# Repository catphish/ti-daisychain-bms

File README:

TI Daisychain BMS Master
========================

BMS master for daisychained bq76PL455A slave modules.

Building the Firmware
=====================

Prerequisites
-------------

The following tools must be installed before building:

- CMake (https://cmake.org/download/)
- Ninja build system (https://github.com/ninja-build/ninja/releases)
- GNU Arm Embedded Toolchain / arm-none-eabi-gcc
  (https://developer.arm.com/tools-and-software/open-source-software/developer-tools/gnu-toolchain/gnu-rm)
- Raspberry Pi Pico SDK (https://github.com/raspberrypi/pico-sdk)
- Raspberry Pi Pico Extras (https://github.com/raspberrypi/pico-extras)

After installing the Pico SDK and Pico Extras, set the following environment
variables so CMake can find them:

  Windows (Command Prompt):
    set PICO_SDK_PATH=C:\path\to\pico-sdk
    set PICO_EXTRAS_PATH=C:\path\to\pico-extras

  Linux / macOS:
    export PICO_SDK_PATH=/path/to/pico-sdk
    export PICO_EXTRAS_PATH=/path/to/pico-extras

Building with VS Code
---------------------

1. Open the firmware-pico folder in VS Code
   (File > Open Folder... > select firmware-pico)
2. Install the recommended extensions when prompted
   (ms-vscode.cmake-tools, ms-vscode.cpptools, marus25.cortex-debug,
    raspberry-pi.raspberry-pi-pico)
3. When prompted, select the ARM GCC toolchain kit
4. Run Terminal > Run Build Task (Ctrl+Shift+B) to configure and build

The compiled firmware files (bms.uf2, bms.elf, etc.) will be placed in the
firmware-pico/build directory.

Building from the Command Line
-------------------------------

The following commands use the same build flags as settings.json. If you
change cmake.buildDirectory or cmake.configureArgs in settings.json, update
these commands accordingly:

  cd firmware-pico
  cmake -B build -G Ninja -DPICO_BOARD=pico -DCMAKE_BUILD_TYPE=Release
  cmake --build build

Uploading to the Pico
---------------------

Hold the BOOTSEL button on the Pico and connect it to your PC via USB. It
will appear as a mass-storage device (RPI-RP2). Copy firmware-pico/build/bms.uf2
to that drive. The Pico will reboot and run the new firmware automatically.

This board will communicate with up to 3 strings of bq76PL455A battery
modules. Each string supports up to 16 modules, and each module supports
up to 16 cells. A common configuration is 3 strings of 6 modules but any
combination is supported.

The board will read the voltages of all detected cells and will perform
balancing as well as reporting data over CAN.

Connector J1
=============

------------------------
| CANH | WAKE1 | WAKE2 |
| CANL |  GND  |  +12V |
------------------------

The low voltage connector J1 has 3 functions:

1) Connect +12v to a permanent positive suppy (5v - 14v)
2) Connect CANH and CANL to a CAN bus.
3) Connect WAKE1 and WAKE2 to switched voltage sources

If either WAKE1 OR WAKE2 is live (+5v to +14v) theh the board will wake
up and monitor the pack. If both are off (0v) then the board will finish
any in-progress balancing, then go into a low power sleep mode.

It is recommended to connect WAKE1 to ignition live, and WAKE2 to a 12V
output generated by a charger. This will ensure that the cells are monitored
during both charge and discharge.

Connector J2, J3, J4
====================

Each of the BATT1, BATT2 and BATT3 (J2,J3,J4) may be connected to the data
pins of a bq76PL455A battery module. All three are optional, and all three
support a full chain of up to 16 battery modules, or any partial chain.
Chain lengths do not have to be matched. The pinout of the battery module
is beyong the scope of this document.

Power Modes
===========

When either WAKE1 or WAKE2 are high, the module will enter active mode. In
this mode, it will continuously monitor the voltage of all attached cells.
Data including the pack voltage, high and low cell voltages, and temperatures
will be send to the CAN bus at 1 second intervals. Balancing will take place
if necessary. For further details of balancing see the next section.

When WAKE1 and WAKE2 are both low, and balancing is complete, the board will
enter a low power sleep mode. In this mode, the board consumes approximately
600uA (0.6mA) at 12V and will perform no actions until woken again. The
bq76PL455A modules will also anter a low power state, consuming close to zero
power from the high voltage pack.

Balancing
=========

If any cell voltage is detected as being higher than 4.0V and more than 10mV
higher than the lowest recorded cell voltage, it will be bled until one of
these ocnditions is no longer met. To prevent excessive heat, only one cell
in each battery (16 cell module) will be bled simultaneously. If multiple cells
meet the criteria, the cell with the highest voltage will be selected.
Balancing will be considered complete when no cells meet the criteria for
balancing.

CAN Messages Received
=====================

This modules does not receive CAN messages.

CAN Messages Sent
=================

--------------------------------------------------------------------------------
| CAN ID | Byte 0-3           | Byte 4-5          | Byte 6      | Byte 7       |
| 0x4f0  | Total Pack Voltage | Balance Threshold | Error count | Module count |
--------------------------------------------------------------------------------

Total pack voltage it the sum of all modules. For parallel packs this value
will be a multiple of the real pack voltage.

Balance threshold will be a non-zero value when balancing is active and
indicates the target voltage, generally this will be 10mV higher than the
minimum cell voltage.

--------------------------------------------------------------------
| CAN ID | Byte 0-1   | Byte 2-3   | Byte 4-5      | Byte 6-7      |
| 0x4f1  | Max Cell V | Min Cell V | Max Cell Temp | Min Cell Temp |
--------------------------------------------------------------------

All values are big endian. Voltage values should be interpreted by dividing
the value by 13107. Temperature values are 

The following calculation can be used to convert the readong for an External NTC to a temperature:

float temperature(uint16_t adc) {
  float r = 0.0000000347363427499292f * adc * adc - 0.001025770762903f * adc + 2.68235340614337f;
  float t = log(r) * -30.5280964239816f + 95.6841501312447f;
  return t;
}

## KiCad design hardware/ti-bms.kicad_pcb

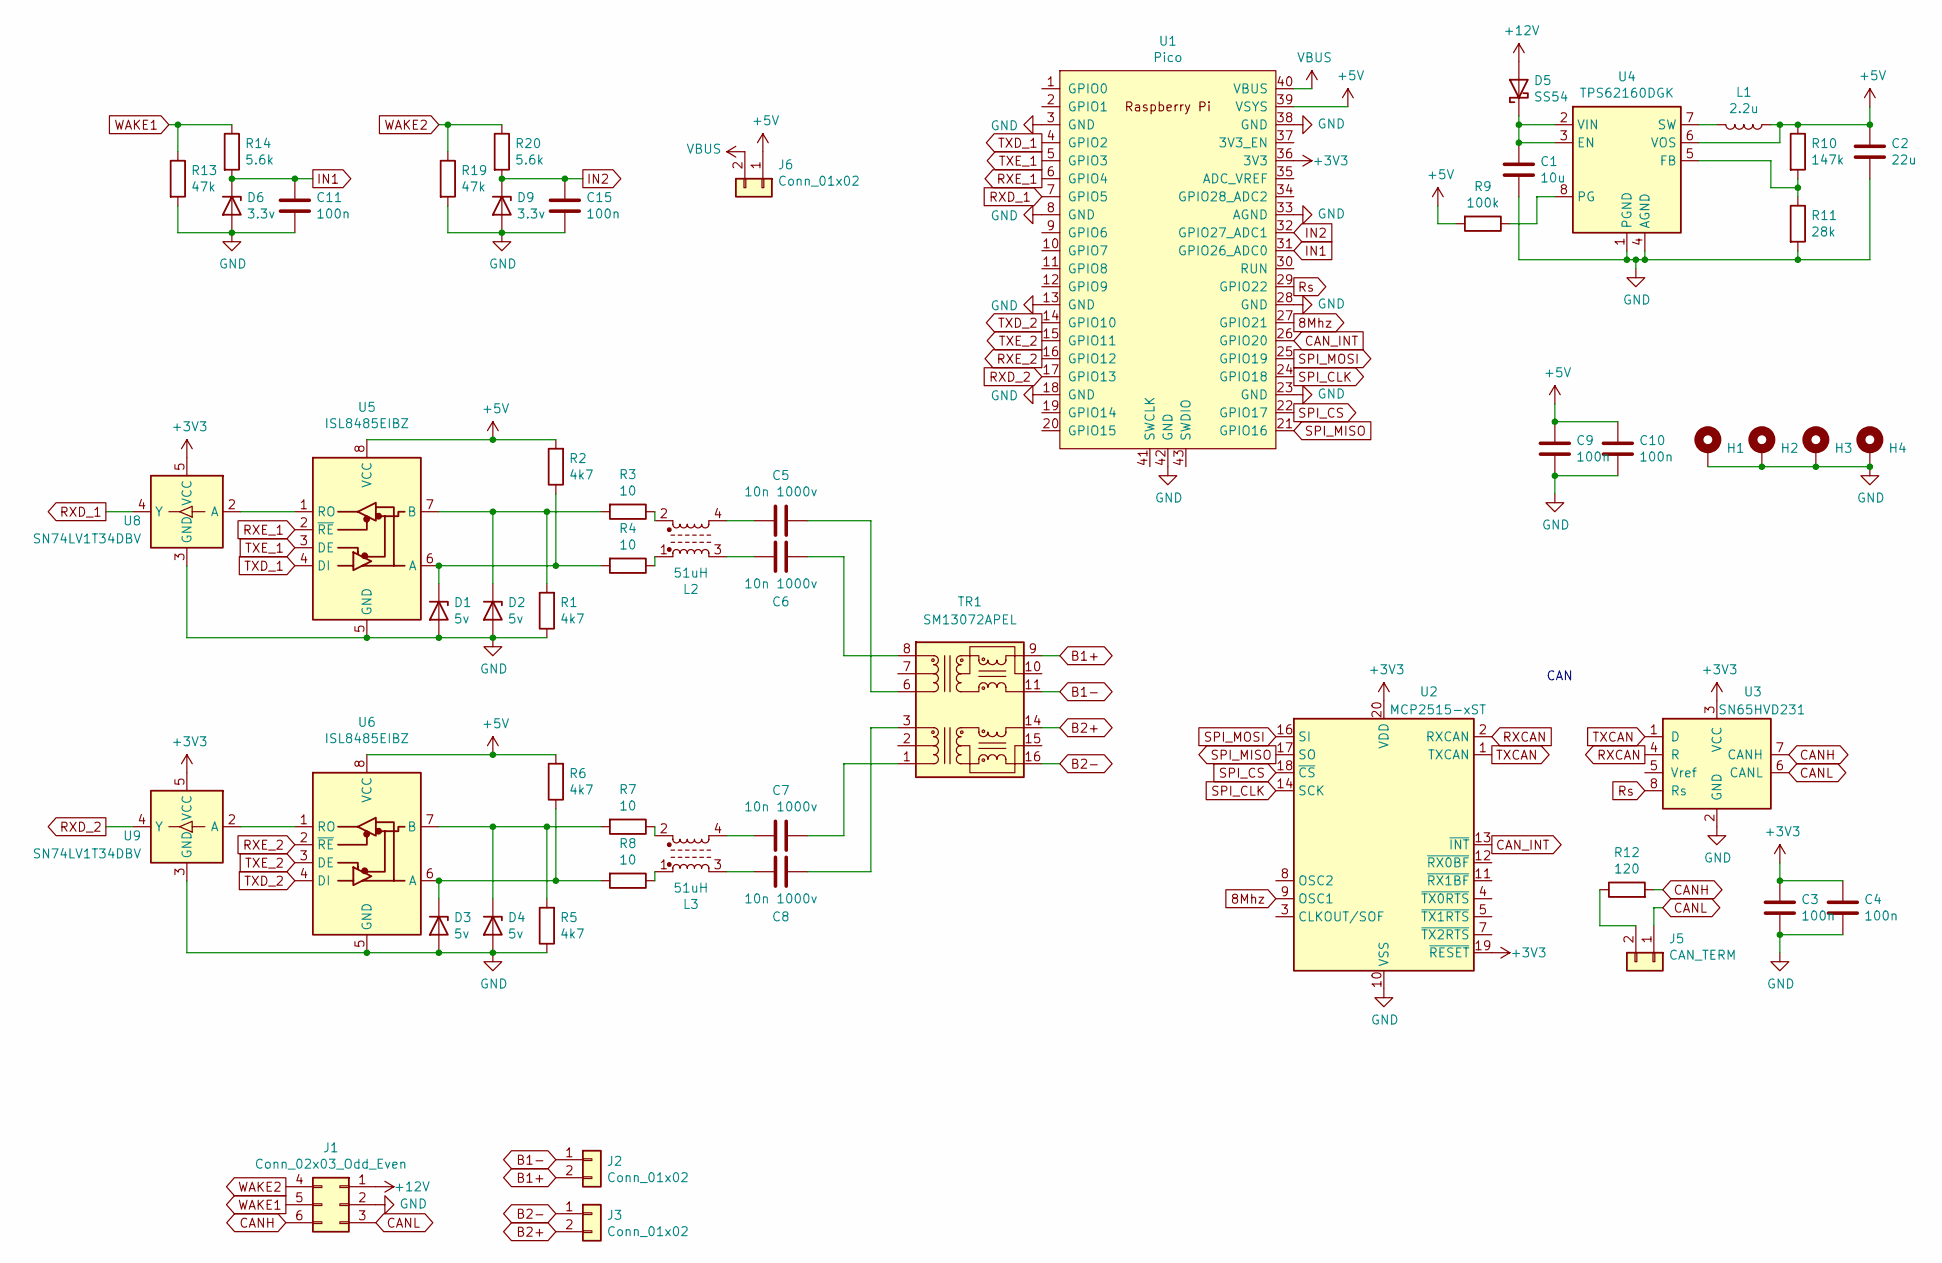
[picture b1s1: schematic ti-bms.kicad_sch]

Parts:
C1: 10u; C_1210_3225Metric; LCSC C77102
C2: 22u; C_1206_3216Metric; LCSC C5672
C3, C4, C9, C10, C11, C15: 100n; C_0603_1608Metric; LCSC C14663
C5, C6, C7, C8: 10n 1000v; C_1206_3216Metric; LCSC C9194
D1, D2, D3, D4: 5v; SOD882; LCSC C85401
D5: SS54; D_SMA; LCSC C22452
D6, D9: 3.3v; D_MiniMELF; LCSC C8056
H1, H2, H3, H4: MountingHole; MountingHole_3.2mm_M3_Pad
J1: Conn_02x03_Odd_Even; Molex_Micro-Fit_3.0_43045-0600_2x03_P3.00mm_Horizontal
J2, J3: Conn_01x02; Molex_Micro-Fit_3.0_43650-0200_1x02_P3.00mm_Horizontal
J5: CAN_TERM; PinHeader_1x02_P2.54mm_Vertical
J6: Conn_01x02; PinHeader_1x02_P2.54mm_Vertical
L1: 2.2u; L_Neosid_SMS-ME3015; LCSC C43389
L2, L3: 51uH; ACT45B-101-2P-TL003; LCSC C76584
R1, R2, R5, R6: 4k7; R_0603_1608Metric; LCSC C23162
R3, R4, R7, R8: 10; R_0603_1608Metric; LCSC C22859
R9: 100k; R_0603_1608Metric; LCSC C25803
R10: 147k; R_0603_1608Metric; LCSC C22878
R11: 28k; R_0603_1608Metric; LCSC C22989
R12: 120; R_1206_3216Metric; LCSC C17909
R13, R19: 47k; R_0603_1608Metric; LCSC C25819
R14, R20: 5.6k; R_0603_1608Metric; LCSC C23189
TR1: SM13072APEL; Transformer_Ethernet_Wuerth_749013011A; LCSC C129155
U1: Pico; RPi_Pico_SMD_TH
U2: MCP2515-xST; TSSOP-20_4.4x6.5mm_P0.65mm; LCSC C15193
U3: SN65HVD231; SOIC-8_3.9x4.9mm_P1.27mm; LCSC C129257
U4: TPS62160DGK; MSOP-8_3x3mm_P0.65mm; LCSC C60726
U5, U6: ISL8485EIBZ; SOP-8_3.9x4.9mm_P1.27mm; LCSC C382024
U8, U9: SN74LV1T34DBV; SOT-23-5; LCSC C100024

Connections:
8Mhz: U1.27 (GPIO21), U2.9 (OSC1)
+3V3: C3.1, C4.1, U1.36 (3V3), U2.19 (~RESET), U2.20 (VDD), U3.3 (VCC), U8.5 (VCC), U9.5 (VCC)
+5V: C2.1, C9.1, C10.1, J6.1, L1.1, R2.2, R6.2, R9.2, R10.1, U1.39 (VSYS), U4.6 (VOS), U5.8 (VCC), U6.8 (VCC)
+12V: D5.2 (A), J1.1
B1+: J2.2, TR1.9 (RX-)
B1-: J2.1, TR1.11 (RX+)
B2+: J3.2, TR1.14 (TX-)
B2-: J3.1, TR1.16 (TX+)
CANH: J1.6, R12.2, U3.7 (CANH)
CANL: J1.3, J5.1, U3.6 (CANL)
CAN_INT: U1.26 (GPIO20), U2.13 (~INT)
GND: C1.2, C2.2, C3.2, C4.2, C9.2, C10.2, C11.2, C15.2, D1.2 (A), D2.2 (A), D3.2 (A), D4.2 (A), D6.2 (A), D9.2 (A), H1.1, H2.1, H3.1, H4.1, J1.2, R1.1, R5.1, R11.2, R13.2, R19.2, U1.3 (GND), U1.8 (GND), U1.13 (GND), U1.18 (GND), U1.23 (GND), U1.28 (GND), U1.33 (AGND), U1.38 (GND), U1.42 (GND), U2.10 (VSS), U3.2 (GND), U4.1 (PGND), U4.4 (AGND), U5.5 (GND), U6.5 (GND), U8.3 (GND), U9.3 (GND)
IN1: C11.1, D6.1 (K), R14.2, U1.31 (GPIO26_ADC0)
IN2: C15.1, D9.1 (K), R20.2, U1.32 (GPIO27_ADC1)
unnamed: C1.1, D5.1 (K), U4.2 (VIN), U4.3 (EN)
unnamed: C5.1, TR1.6 (RD+)
unnamed: C5.2, L2.4
unnamed: C6.1, TR1.8 (RD-)
unnamed: C6.2, L2.3
unnamed: C7.1, TR1.1 (TD+)
unnamed: C7.2, L3.4
unnamed: C8.1, TR1.3 (TD-)
unnamed: C8.2, L3.3
unnamed: D1.1 (K), R2.1, R4.2, U5.6 (A)
unnamed: D2.1 (K), R1.2, R3.2, U5.7 (B)
unnamed: D3.1 (K), R6.1, R8.2, U6.6 (A)
unnamed: D4.1 (K), R5.2, R7.2, U6.7 (B)
unnamed: J5.2, R12.1
unnamed: L1.2, U4.7 (SW)
unnamed: L2.1, R4.1
unnamed: L2.2, R3.1
unnamed: L3.1, R8.1
unnamed: L3.2, R7.1
unnamed: R9.1, U4.8 (PG)
unnamed: R10.2, R11.1, U4.5 (FB)
unnamed: U5.1 (RO), U8.2 (A)
unnamed: U6.1 (RO), U9.2 (A)
RXCAN: U2.2 (RXCAN), U3.4 (R)
RXD_1: U1.7 (GPIO5), U8.4 (Y)
RXD_2: U1.17 (GPIO13), U9.4 (Y)
RXE_1: U1.6 (GPIO4), U5.2 (~RE)
RXE_2: U1.16 (GPIO12), U6.2 (~RE)
Rs: U1.29 (GPIO22), U3.8 (Rs)
SPI_CLK: U1.24 (GPIO18), U2.14 (SCK)
SPI_CS: U1.22 (GPIO17), U2.18 (~CS)
SPI_MISO: U1.21 (GPIO16), U2.17 (SO)
SPI_MOSI: U1.25 (GPIO19), U2.16 (SI)
TXCAN: U2.1 (TXCAN), U3.1 (D)
TXD_1: U1.4 (GPIO2), U5.4 (DI)
TXD_2: U1.14 (GPIO10), U6.4 (DI)
TXE_1: U1.5 (GPIO3), U5.3 (DE)
TXE_2: U1.15 (GPIO11), U6.3 (DE)
VBUS: J6.2, U1.40 (VBUS)
WAKE1: J1.5, R13.1, R14.1
WAKE2: J1.4, R19.1, R20.1

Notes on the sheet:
CAN

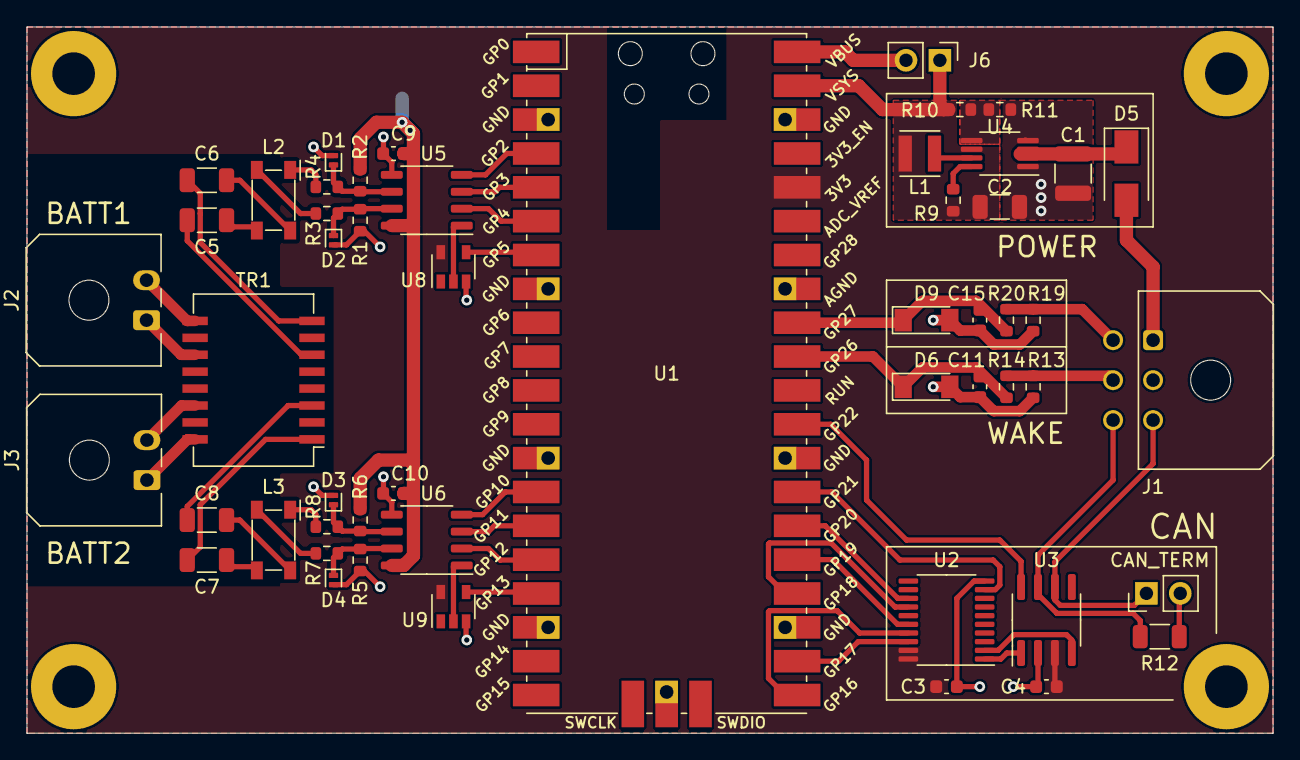
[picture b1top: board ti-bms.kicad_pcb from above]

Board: 2 copper layers, 93.5 x 53.0 mm, 56 parts (0 on the bottom side), 55 nets.

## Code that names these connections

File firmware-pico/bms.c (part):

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#define MAX_MODULES (16 * CHAIN_COUNT)

// Hardware wakeup pins
#define WAKE1 26
#define WAKE2 27

// Define pins for SPI (to CAN)
#define SPI_PORT spi0
#define SPI_MISO 16
#define SPI_CS 17
#define SPI_CLK 18
#define SPI_MOSI 19
#define CAN_INT 20    // Interrupt from CAN controller
#define CAN_CLK 21    // 8MHz clock for CAN
#define CAN_SLEEP 22  // Shut down CAN transceiver

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void SPI_configure() {
  spi_init(SPI_PORT, 1000000);
  spi_set_format(SPI_PORT, 8, 0, 0, SPI_MSB_FIRST);
  gpio_set_function(SPI_MISO, GPIO_FUNC_SPI);
  gpio_set_function(SPI_MOSI, GPIO_FUNC_SPI);
  gpio_set_function(SPI_CLK, GPIO_FUNC_SPI);
  gpio_init(SPI_CS);
  gpio_set_dir(SPI_CS, GPIO_OUT);
  gpio_put(SPI_CS, 1);
}

void CAN_reset() {
  gpio_put(SPI_CS, 0);
  spi_write_blocking(SPI_PORT, (uint8_t[]){CMD_RESET}, 1);
  gpio_put(SPI_CS, 1);
  busy_wait_us(100);
}

uint8_t CAN_reg_read(uint8_t reg) {
  uint8_t data;
  gpio_put(SPI_CS, 0);
  spi_write_blocking(SPI_PORT, (uint8_t[]){CMD_READ, reg}, 2);
  spi_read_blocking(SPI_PORT, 0, &data, 1);
  gpio_put(SPI_CS, 1);
  return (data);
}

void CAN_reg_write(uint8_t reg, uint8_t val) {
  gpio_put(SPI_CS, 0);
  spi_write_blocking(SPI_PORT, (uint8_t[]){CMD_WRITE, reg, val}, 3);
  gpio_put(SPI_CS, 1);
}

void CAN_reg_modify(uint8_t reg, uint8_t mask, uint8_t val) {
  gpio_put(SPI_CS, 0);
  busy_wait_us(2);
  spi_write_blocking(SPI_PORT, (uint8_t[]){CMD_MODIFY, reg, mask, val}, 4);
  busy_wait_us(2);
  gpio_put(SPI_CS, 1);
}

void CAN_configure(uint16_t id) {
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  CAN_reg_write(REG_CANCTRL, MODE_SLEEP);
  gpio_put(CAN_SLEEP, 1);  // Sleep the CAN transceiver
  uint32_t s = save_and_disable_interrupts();
  gpio_set_irq_enabled_with_callback(WAKE1, GPIO_IRQ_LEVEL_HIGH, true, &gpio_callback);
  gpio_set_irq_enabled_with_callback(WAKE2, GPIO_IRQ_LEVEL_HIGH, true, &gpio_callback);
  gpio_set_dormant_irq_enabled(WAKE1, GPIO_IRQ_LEVEL_HIGH, true);
  gpio_set_dormant_irq_enabled(WAKE2, GPIO_IRQ_LEVEL_HIGH, true);
  clocks_hw->sleep_en0 = 0;
  clocks_hw->sleep_en1 = 0;
  xosc_dormant();
  reconfigure_clocks();
  gpio_set_irq_enabled_with_callback(WAKE1, GPIO_IRQ_LEVEL_HIGH, false, &gpio_callback);
  gpio_set_irq_enabled_with_callback(WAKE2, GPIO_IRQ_LEVEL_HIGH, false, &gpio_callback);
  restore_interrupts(s);
  SPI_configure();
  gpio_put(CAN_SLEEP, 0);  // Wake the CAN transceiver
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  }

  // Configure hardware wakeup pins
  gpio_init(WAKE1);
  gpio_init(WAKE2);
  gpio_set_dir(WAKE1, GPIO_IN);
  gpio_set_dir(WAKE2, GPIO_IN);
  gpio_disable_pulls(WAKE1);
  gpio_disable_pulls(WAKE2);

  // Configure CAN transceiver sleep line
  gpio_init(CAN_SLEEP);
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    // Sleep for a minimum of 500ms second per loop.
    sleep_ms(500);
    // If there's no reason to be awake, go into very low power sleep
    if (!balance_threshold && !gpio_get(WAKE1) && !gpio_get(WAKE2) && usb_suspended()) {
      sleep_modules();
      deep_sleep();
      rewake = 1;
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
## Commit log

2021-12-23 initial comit
2021-12-24 remove fill from isolated area
2021-12-24 add missing 3d models
2021-12-24 more on isolation
2022-01-02 add firmware
2022-01-04 add readme, add CAN based wakeup
2022-01-04 correct voltage conversion value
2022-01-08 add 12v input and output, connect CAN line driver sleep pin
2022-01-10 dual wake inputs
2022-01-10 update schematic and picture
2022-01-12 rework inputs
2022-01-13 finish inputs
2022-01-25 swap in available part
2022-01-25 finish v3 firmware
2022-01-25 remove old readme
2022-01-30 correct module counting
2022-02-03 v3 readme
2022-02-03 WAKE1 and WAKE2 recommendation
2022-04-01 USB info output
2022-05-10 output temperature data to usb, hardcode cell count, enable RX checksums
2022-05-10 check RX CRC
2022-05-12 housekeeping
2022-05-13 add usb mode, remove superfluous code, fix receive timing, detect false start bits, hardcode module count
2022-05-13 keep it simple for now!
2022-05-13 readd simple false start bit check
2022-05-15 v4 hardware with 5v line drivers
2022-05-21 refactor low power sleep
2022-05-22 print temperatures in USB mode
2022-05-24 add missing trace
2022-05-24 change resistor value, better error logging, remove redundant code
2022-05-31 move all configurable items to top of code
2022-06-01 remove static USB mode, replace with dynamic USB detection
2022-06-01 tidying only
2022-07-07 reformatting
2022-07-07 remove unnecessary debug output, minor timing improvements
2022-07-13 tidying
2022-07-14 transmit slow loop of individual cell voltages
2022-07-18 multi-cell balancing
2022-09-21 integrate transformer for more common mode rejection
2022-12-28 simplify formatting
2026-03-29 Initial plan
2026-03-29 Add VS Code build config and setup instructions to fix Pico compile issue on Windows
    Agent-Logs-Url: https://github.com/catphish/ti-daisychain-bms/sessions/4c6bb995-5a95-4b8b-a8af-07bcdd38f8ec
